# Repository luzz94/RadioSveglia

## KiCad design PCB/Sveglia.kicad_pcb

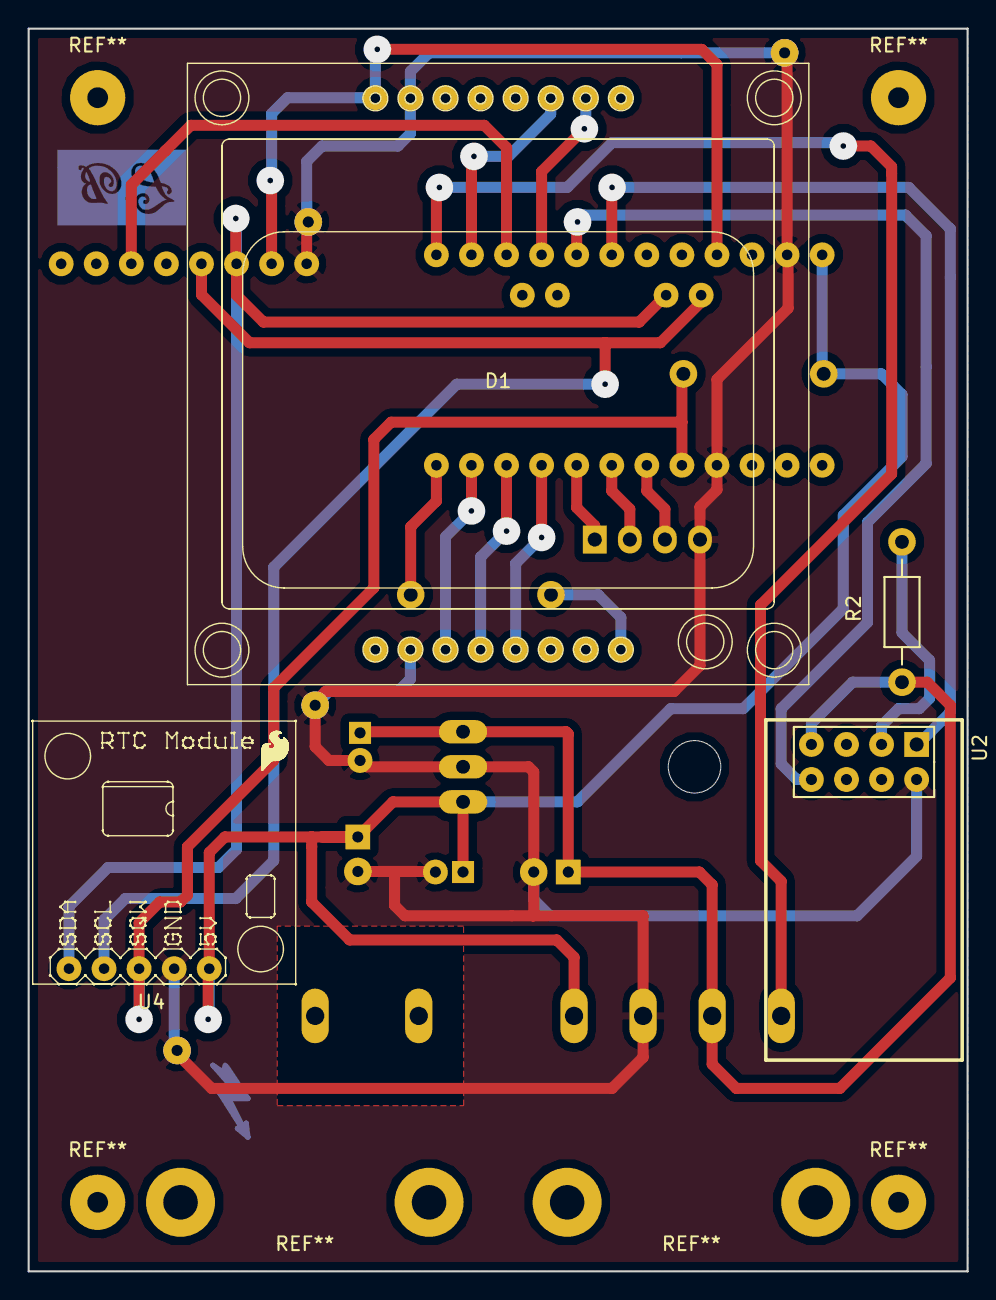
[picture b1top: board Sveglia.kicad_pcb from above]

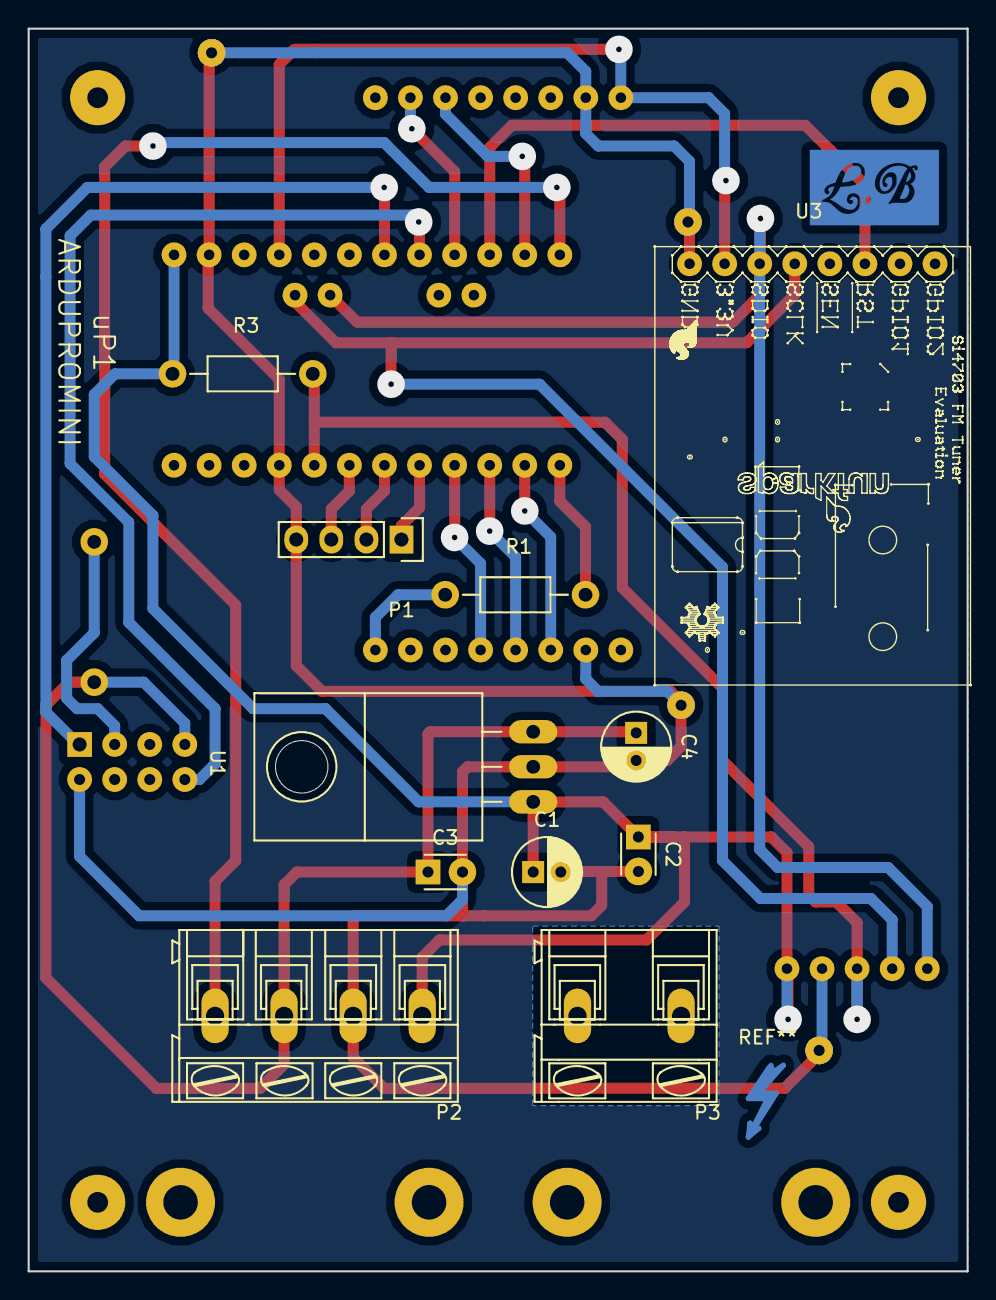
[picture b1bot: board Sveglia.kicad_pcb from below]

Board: 2 copper layers, 68.0 x 90.0 mm, 16 parts (12 on the bottom side), 22 nets.

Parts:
C1, C4: 22μF; C_Radial_D5_L11_P2
C2, C3: 1nF; C_Disc_D3_P2.5
D1: Nokia3310_SparkFun
P1: Rotary_Conn; Socket_Strip_Straight_1x04
P2: CONN_01X04; AK300-4
P3: CONN_01X02; AK300-2_LARGE
R1: 390Ω; Resistor_Horizontal_RM10mm
R2: 3K3; Resistor_Horizontal_RM10mm
R3: 10K; Resistor_Horizontal_RM10mm
U1: 7833; TO-220_Neutral123_Horizontal_LargePads
U2: ESP-01v090; ESP-01
U3: Si4703_Module
U4: SparkFun_RTC_Module
uP1: ARDUPROMINI; ArduProMini

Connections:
+3V3: D1.1, U3.7, uP1.22
+5V: C1.1, C2.1, P2.1, R3.1, U1.1, U4.5, uP1.19
/3V3_ESP: C3.1, C4.1, P2.3, R2.1, U1.3, U2.7
/PWM_OUT: P2.4, uP1.30
/SQW: R3.2, U4.3, uP1.11
GNDPWR: C1.2, C2.2, C3.2, C4.2, D1.2, P1.4, P2.2, U1.2, U2.2, U3.8, U4.4, uP1.10, uP1.20
unnamed: D1.3, uP1.17
unnamed: D1.4, uP1.16
unnamed: D1.5, uP1.15
unnamed: D1.6, uP1.29
unnamed: D1.7, uP1.27
unnamed: D1.8, R1.1
unnamed: P1.1, uP1.14
unnamed: P1.2, uP1.13
unnamed: P1.3, uP1.12
unnamed: R1.2, uP1.18
unnamed: R2.2, U2.3
unnamed: U2.1, uP1.25
unnamed: U2.8, uP1.26
unnamed: U3.3, uP1.28
unnamed: U3.5, U4.2, uP1.32
unnamed: U3.6, U4.1, uP1.31

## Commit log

2016-10-06 Create Main
2016-10-09 Create help
